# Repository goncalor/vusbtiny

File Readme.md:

# Introduction

VUSBtiny is a small in-system programmer (ISP) for Atmel AVR microcontrollers. It allows you to program microcontrollers on the go, without carrying a big programmer with you.

VUSBtiny is based on the [USBtinyISP](https://learn.adafruit.com/usbtinyisp). It uses an Atmel AVR microcontroller running [V-USB](https://www.obdev.at/products/vusb/index.html), which allows it to communicate with your computer via a USB port.

The programmer was not developed by me, but with this repository I added to it in some ways:

- edited the code so that it compiles with the most recent versions of `avr-gcc`
- designed a PCB for the project, in a way which should make it simple to be hand produced
- wrote this readme, which can help you make your own VUSBtiny.

You can find the original VUSBtiny page [here](https://web.archive.org/web/20180423215321/http://www.simpleavr.com/avr/vusbtiny) (or [here](https://simpleavr.github.io/old_projects/avr_vusbtiny/index.html)).

# License

VUSBtiny is licensed under [GNU GPL v2.0](http://choosealicense.com/licenses/gpl-2.0/). The license is in the file `LICENSE.txt`. The changes I made are released under the same license.

The V-USB driver is licensed under GNU GPL v2.0. If you intend to use V-USB commercially read [this page](https://www.obdev.at/products/vusb/license.html).

# Needed components

To assemble your own VUSBtiny you will need the following components:

- an Atmel AVR microcontroller [compatible with V-USB](https://www.obdev.at/products/vusb/index.html). I suggest ATtiny45 or ATtiny85
- one USB port (male and type A)
- two 68 Ω resistors
- one 1.5 kΩ resistor
- two 3.6 V Zener diodes
- a 10 μF capacitor (optional but recommended)
- a breadboard, perfboard or PCB to assemble the circuit.

# How to flash the AVR

The following instructions teach you how you can flash the Atmel AVR you chose to be the brain of your VUSBtiny. I will assume you are using ATtiny45 or ATtiny85. The instructions should be very similar even if you are using others.

## With an Arduino Uno

1. Choose a microcontroller compatible with V-USB. You can read about the required specs [here](https://www.obdev.at/products/vusb/). You need at least a 2 kB flash and 128 B of RAM. If you don't want to use an external oscillator your microcontroller must have a 16.5 MHz internal RC oscillator.
1. [Setup your Arduino as an ATtiny programmer](http://highlowtech.org/?p=1695)
1. Program Arduino Uno with the "ArduinoISP" sketch. This step is done without the capacitor between the RESET and GND pins of the Arduino. After you upload the "ArduinoISP" sketch connect the capacitor, as described in the link above
1. Adjust the following options in the `makefile`:
    - `MCU=attiny85`, for example
    - possibly adjust `PROGRAMMER_MCU` also. For ATtiny85/45 this is not needed
    - `AVRDUDE_PROGRAMMERID=avrisp`
    - `AVRDUDE_PORT=/dev/ttyACM0` or to whatever port the Arduino Uno is connected to. You check which port to use by running `dmesg` right after you connect your Arduino. The last lines in the output should mention some `tty` port
    - `BAUD=19200`. This value must match the one in the `Serial.begin()` in the "ArduinoISP" example
    - change the fuses if needed (`FUSE_L` and `FUSE_H`)
1. Do `make`. The source should compile successfully
1. Do `make install`
1. Set the fuses (if needed). On ATtiny85/45 we need to disable the reset pin which will be used as a normal I/O pin, which means you will not be able to program this microcontroller anymore using the Arduino Uno. If you need to reverse this step you need a HVSP (High Voltage Serial Programmer).
    - the fuses differ from device to device. The `makefile` is prepared for ATtiny85/45. If you have another MCU search for a fuse calculator that can aid you setting the correct fuses
    - when you're ready run `make fuse`

# How to use your new programmer

Your newly made programmer will be seen as a USBtinyISP programmer. That means the options you give to `avrdude` will be the same as if you had a true USBtinyISP connected. Example (flashing a simple blink code):

	avrdude -c usbtiny -p t85 -U flash:w:blinkC.hex

You may have to run with `sudo`, or set correct options in your system.

# Troubleshooting

1. Checking if your device was recognised

	Little after you connect the VUSBtiny to your computer if you run `dmesg` you should see something like this:

		[27548.612082] usb 4-1.5: new low-speed USB device number 105 using ehci-pci
		[27548.639576] usb 4-1.5: New USB device found, idVendor=1781, idProduct=0c9f
		[27548.639587] usb 4-1.5: New USB device strings: Mfr=0, Product=2, SerialNumber=0
		[27548.639592] usb 4-1.5: Product: USBtinyISP

	If instead you see only error messages this means the VUSBtiny was not correctly recognised, so it will not work. Try reconnecting.

2. When programming with VUSBtiny `avrdude` throws `Operation not permitted` error

		avrdude -c usbtiny -p t85 -U flash:w:blinkC.hex
	
		avrdude: error: usbtiny_transmit: error sending control message: Operation not permitted
		avrdude: initialization failed, rc=-1
		         Double check connections and try again, or use -F to override
		         this check.
	
		avrdude: error: usbtiny_transmit: error sending control message: Operation not permitted
		avrdude done.  Thank you.

	If you see `avrdude` throwing the previous error back atcha it is probably a permissions problem and you have two options:

	- run the command with `sudo` or
	- [write a udev rule](https://mightyohm.com/blog/2010/03/run-avrdude-without-root-privs-in-ubuntu/)

3. When programming with VUSBtiny `avrdude` throws `initialization failed, rc=-1` error

		avrdude -c usbtiny -p t85 -U flash:w:blinkC.hex 

		avrdude: initialization failed, rc=-1
			 Double check connections and try again, or use -F to override
			 this check.

		avrdude done.  Thank you.

	If you see this error you probably made a mistake when hooking up the programmer (VUSBtiny) to the target (whatever microcontroller you are programming). Recheck your connections against a 6-pin ISP header pinout and the MISO, MOSI, SCK, RST, VCC and GND pins of your microcontroller.

# Improvements

Some improvements that should be made to the PCB are:

- leave more space between the capacitor and the ISP headers. This way the capacitor can be bent to be made horizontal without difficulting access to the ISP header pins

- increase spacing between traces. This is meant to ease manual production and soldering of the board

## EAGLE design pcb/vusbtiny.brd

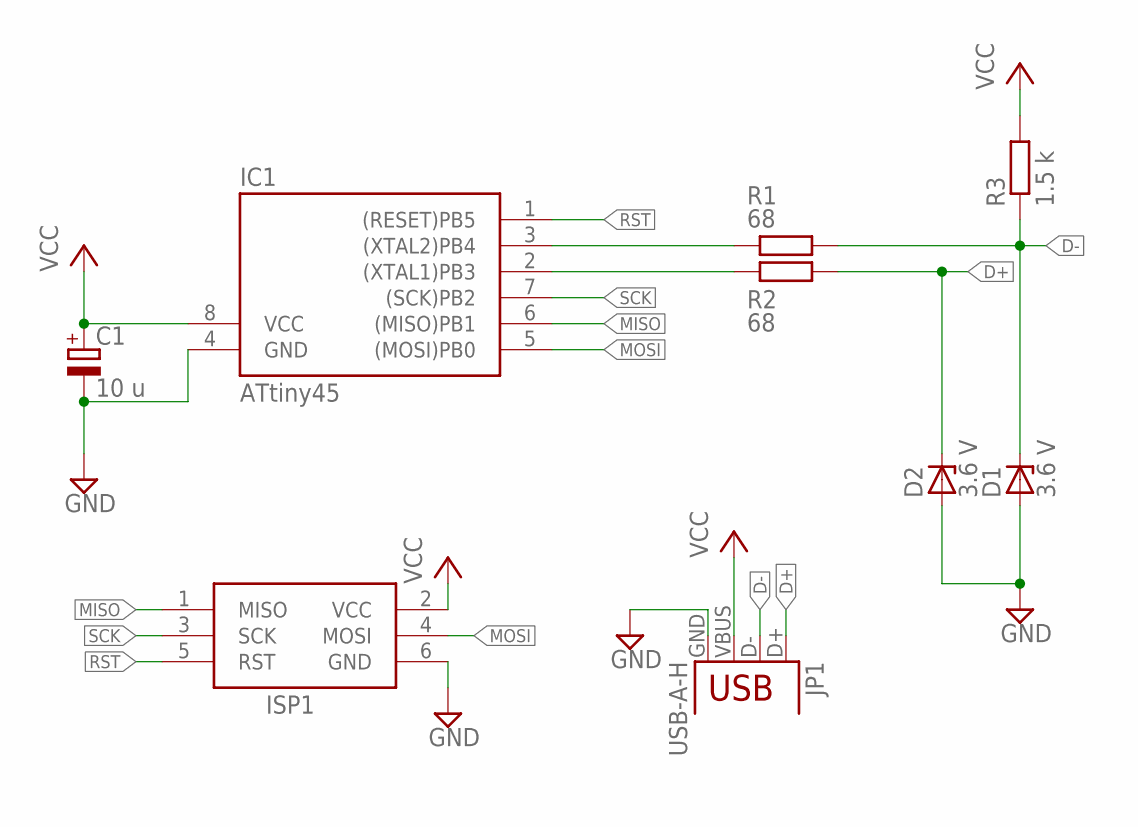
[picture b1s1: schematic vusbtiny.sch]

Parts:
C1: 10 u; E2,5-5
D1, D2: 3.6 V; DO34Z7
IC1: ATtiny45; DIL08
ISP1: AVRISP-6; AVRISP
JP1: USB-A-H
R1, R2: 68; 0207/10
R3: 1.5 k; 0207/10

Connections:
D+: D2.C, JP1.D+, R2.2
D-: D1.C, JP1.D-, R1.2, R3.1
GND: C1.-, D1.A, D2.A, IC1.4 (GND), ISP1.6 (GND), JP1.GND
MISO: IC1.6 ((MISO)PB1), ISP1.1 (MISO)
MOSI: IC1.5 ((MOSI)PB0), ISP1.4 (MOSI)
unnamed: IC1.3 ((XTAL2)PB4), R1.1
unnamed: IC1.2 ((XTAL1)PB3), R2.1
RST: IC1.1 ((RESET)PB5), ISP1.5 (RST)
SCK: IC1.7 ((SCK)PB2), ISP1.3 (SCK)
VCC: C1.+, IC1.8 (VCC), ISP1.2 (VCC), JP1.VBUS, R3.2

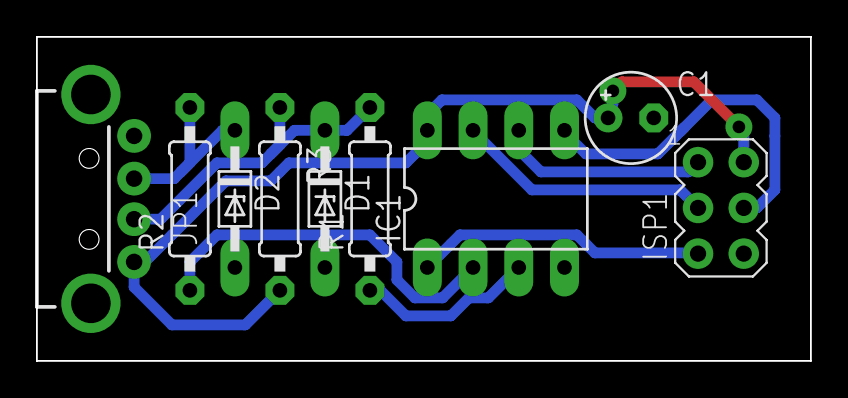
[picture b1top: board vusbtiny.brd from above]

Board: 2 copper layers, 43.0 x 18.0 mm, 9 parts (0 on the bottom side), 10 nets.

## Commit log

2015-06-19 Original, unaltered code.
2015-06-19 Edited code to compile with avr-gcc 4.8.1
2015-06-20 Edited the makefile and added a Readme.
2015-06-20 Updated the Readme. Corrected the USB device name.
2015-06-28 Added hardware files. Placed but still unrouted.
2015-07-04 Reposition components to ease routing. Added DRC.
2015-07-05 Finished routing. Copper pour should be improved.
2015-07-05 Finished routing. Wrote script to make board's pdf
2015-07-06 Added Intro, License, Components to Readme.txt.
2015-08-16 Edited the Readme. Added a blinking LED example.
2020-02-07 Update usbconfig.h
    Added commented lines for inverted D- / D+ lines devices
2021-04-30 Changed VUSBTiny link
    Link changed from "http://www.simpleavr.com/avr/vusbtiny" to "https://simpleavr.github.io/old_projects/avr_vusbtiny/index.html"
2021-05-09 Link to VUSBtiny page archived on Wayback Machine
2023-11-19 Added dependency on usbconfig.h to makefile
    This is especially useful if you e.g. try to change pins used for USB.
2023-11-19 Yet more dependencies on usbconfig.h added
2023-11-30 Added dependency on usbconfig.h to makefile (#8)
    * Added dependency on usbconfig.h to makefile
    This is especially useful if you e.g. try to change pins used for USB.
    * Yet more dependencies on usbconfig.h added

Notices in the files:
parts and their libraries:
SparkFun-Connectors: Licensing: Creative Commons ShareAlike 4.0 International - https://creativecommons.org/licenses/by-sa/4.0
